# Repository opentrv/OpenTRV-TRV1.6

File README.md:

# OpenTRV-TRV1.6
TRV1.6 smart thermostatic radiator valve hardware and software,
evolved from TRV1.5/REV7.

A 'V0p2' type (ATmega328P) board with an alternative motor driver.

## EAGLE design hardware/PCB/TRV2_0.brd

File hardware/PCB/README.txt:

Location for TRV2 schematic and PCB.

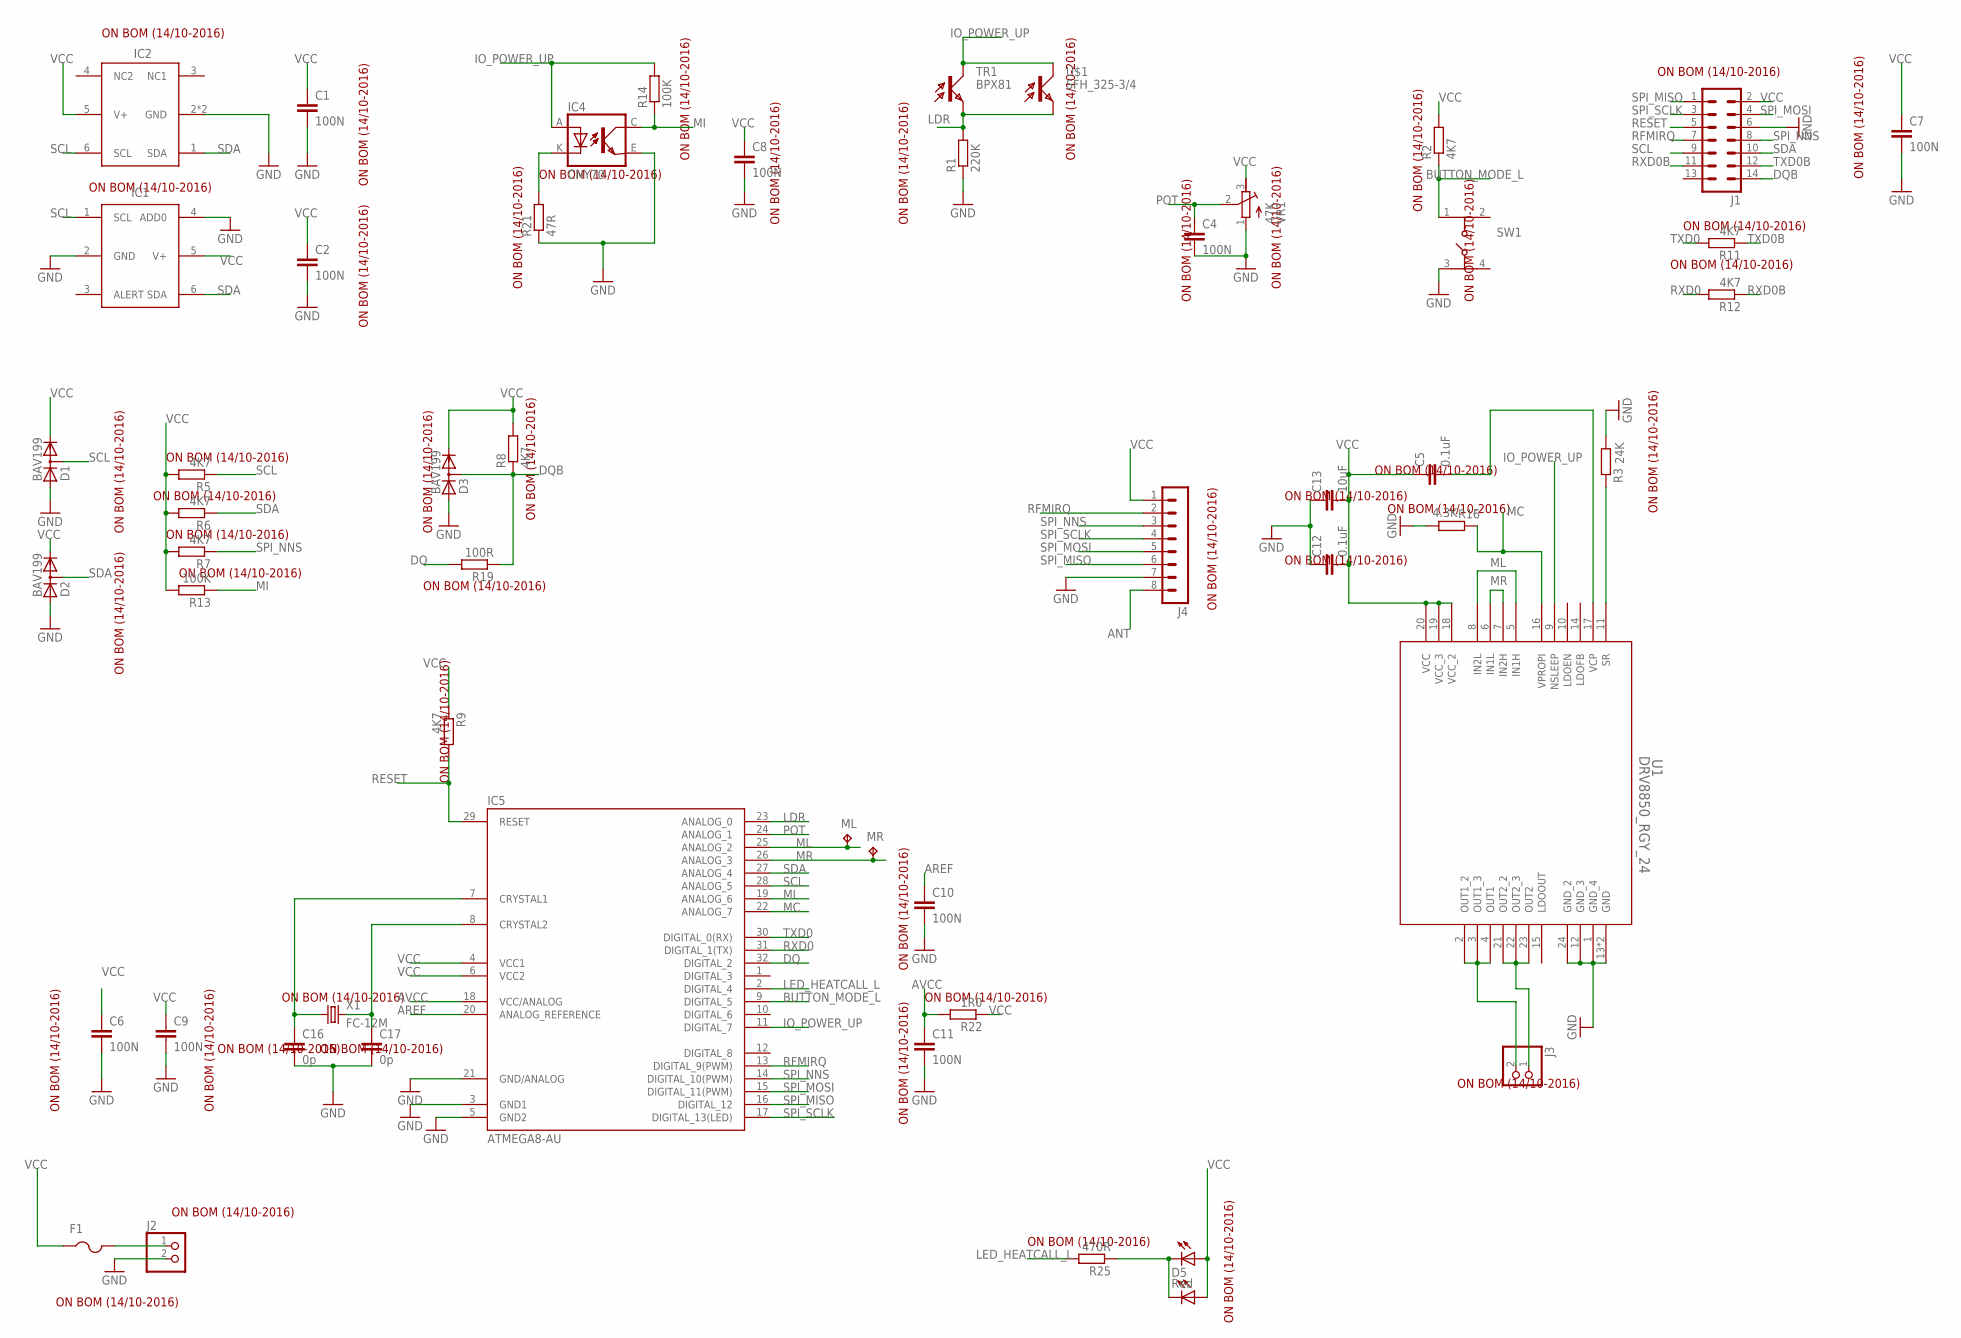
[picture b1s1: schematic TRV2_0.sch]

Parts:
C1, C2, C4, C6, C7, C8, C9, C10, C11: 100N; C0603
C5, C12: 0.1uF; C0603
C13: 10uF; C0603
C16, C17: 0p; C0603
D1, D2, D3: BAV199; SOT23
D5: Red; LED3MM
F1: PTCFUSE-0603; CHIPLED-0603-TTW
IC1: TMP112
IC2: IC2; SHT21
IC4: CNY70; 4
IC5: ATMEGA8-AU; TQFP32-08
J1: MA07-2
J2, J3: PINHD-1X2; 1X02
J4: MA08-1
ML: TPB1,27; B1,27
MR: TPB1,27; B1,27
R1: 220K; R0603
R2, R5, R6, R7, R8, R9, R11, R12: 4K7; R0603
R3: 24K; R0603
R13, R14: 100K; R0603
R16: 4.3K; R0603
R19: 100R; R0603
R21: 47R; R0603
R22: 1R0; R0603
R25: 470R; R0603
SW1: 434331013822
TR1: BPX81
U1: DRV8850_RGY_24; RGY_24
U$1: SFH_325-3/4
U$2: KINGBRIGHTSIDELED
VR1: 47K; RTRIM3296W
X1: FC-12M

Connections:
ANT: J4.8
AREF: C10.1, IC5.20 (ANALOG_REFERENCE)
AVCC: C11.1, IC5.18 (VCC/ANALOG), R22.2
BUTTON_MODE_L: IC5.9 (DIGITAL_5), R2.1, SW1.1
DQ: IC5.32 (DIGITAL_2), R19.2
DQB: D3.3 (AC), J1.14, R8.1, R19.1
GND: C1.2, C2.2, C4.2, C6.2, C7.2, C8.2, C9.2, C10.2, C11.2, C12.1, C13.1, C16.2, C17.2, D1.1 (A), D2.1 (A), D3.1 (A), IC1.2 (GND), IC1.4 (ADD0), IC2.2 (GND), IC2.P$1 (GND), IC4.E (EMI), IC5.3 (GND1), IC5.5 (GND2), IC5.21 (GND/ANALOG), J1.6, J2.2, J4.7, R1.1, R3.1, R16.1, R21.1, SW1.3, U1.1 (GND_4), U1.12 (GND_3), U1.13 (GND), U1.24 (GND_2), U1.25 (GND), VR1.1 (A)
IO_POWER_UP: IC4.A, IC5.11 (DIGITAL_7), R14.2, TR1.C, U1.9 (NSLEEP), U$1.P$2 (C)
LDR: IC5.23 (ANALOG_0), R1.2, TR1.E, U$1.P$1 (E)
LED_HEATCALL_L: IC5.2 (DIGITAL_4), R25.2
MC: IC5.22 (ANALOG_7), R16.2, U1.16 (VPROPI)
MI: IC4.C (COL), IC5.19 (ANALOG_6), R13.1, R14.1
ML: IC5.25 (ANALOG_2), ML.TP, U1.5 (IN1H), U1.8 (IN2L)
MR: IC5.26 (ANALOG_3), MR.TP, U1.6 (IN1L), U1.7 (IN2H)
unnamed: IC4.K (C), R21.2
unnamed: J3.2, U1.2 (OUT1_2), U1.3 (OUT1_3), U1.4 (OUT1)
unnamed: C16.1, IC5.7 (CRYSTAL1), X1.1
unnamed: C17.1, IC5.8 (CRYSTAL2), X1.2
unnamed: D5.K (C), R25.1, U$2.C
unnamed: F1.C (2), J2.1
unnamed: J3.1, U1.21 (OUT2_2), U1.22 (OUT2_3), U1.23 (OUT2)
unnamed: R3.2, U1.11 (SR)
unnamed: C5.2, U1.17 (VCP)
POT: C4.1, IC5.24 (ANALOG_1), VR1.2 (S)
RESET: IC5.29 (RESET), J1.5, R9.2
RFMIRQ: IC5.13 (DIGITAL_9(PWM)), J1.7, J4.2
RXD0: IC5.31 (DIGITAL_1(TX)), R12.2
RXD0B: J1.11, R12.1
SCL: D1.3 (AC), IC1.1 (SCL), IC2.6 (SCL), IC5.28 (ANALOG_5), J1.9, R5.1
SDA: D2.3 (AC), IC1.6 (SDA), IC2.1 (SDA), IC5.27 (ANALOG_4), J1.10, R6.1
SPI_MISO: IC5.16 (DIGITAL_12), J1.1, J4.6
SPI_MOSI: IC5.15 (DIGITAL_11(PWM)), J1.4, J4.5
SPI_NNS: IC5.14 (DIGITAL_10(PWM)), J1.8, J4.3, R7.1
SPI_SCLK: IC5.17 (DIGITAL_13(LED)), J1.3, J4.4
TXD0: IC5.30 (DIGITAL_0(RX)), R11.2
TXD0B: J1.12, R11.1
VCC: C1.1, C2.1, C5.1, C6.1, C7.1, C8.1, C9.1, C12.2, C13.2, D1.2 (C), D2.2 (C), D3.2 (C), D5.A, F1.A (1), IC1.5 (V+), IC2.5 (V+), IC5.4 (VCC1), IC5.6 (VCC2), J1.2, J4.1, R2.2, R5.2, R6.2, R7.2, R8.2, R9.1, R13.2, R22.1, U1.18 (VCC_2), U1.19 (VCC_3), U1.20 (VCC), U$2.A, VR1.3 (E)

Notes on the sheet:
IC2
IC1
ON BOM (14/10-2016)

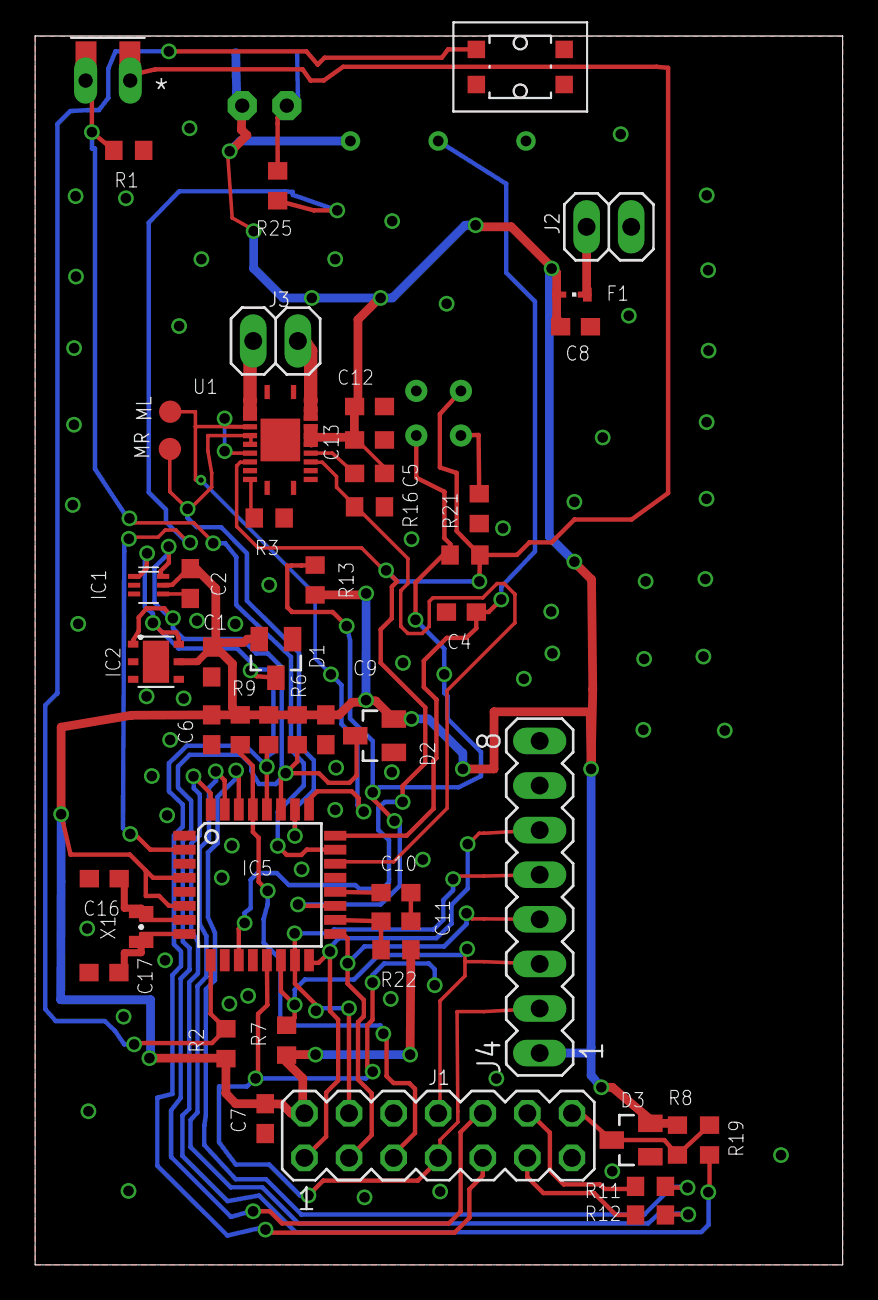
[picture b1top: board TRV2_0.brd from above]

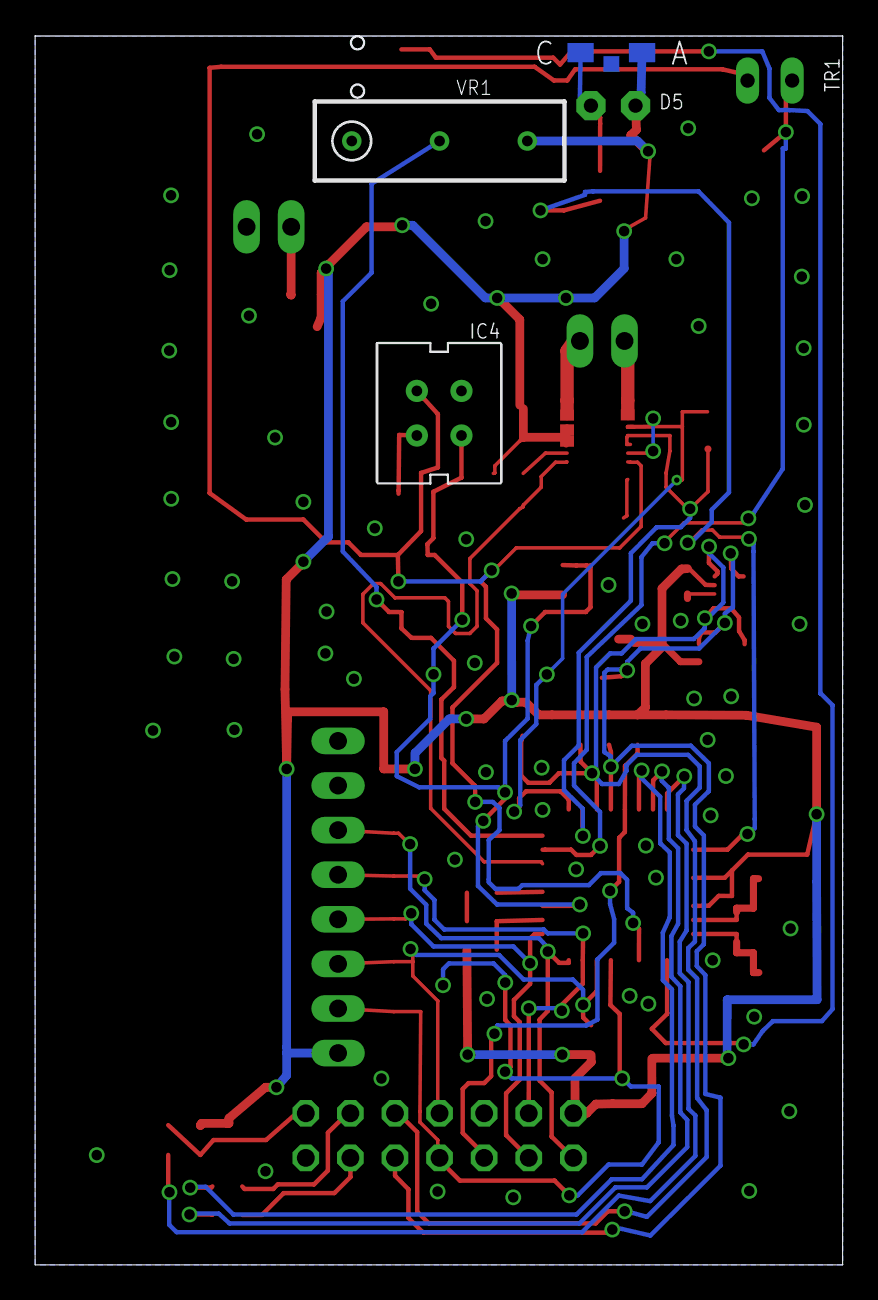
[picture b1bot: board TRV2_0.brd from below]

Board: 2 copper layers, 46.0 x 70.0 mm, 53 parts (5 on the bottom side), 36 nets.

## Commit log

2016-10-02 Convert to Eclipse general project.
2016-10-03 Create place for PCB.
2016-10-04 Schematic done
    NOTE: INT on light sensor not found anywhere else on schematic.
    NOTE: Comms connector differs from Standard.
2016-10-04 double checked schematic
2016-10-04 Typo + more explanation.
2016-10-04 first draft of board added
2016-10-04 Componets rotated and locked
    locked as they now point the same way as the one made by enlight
2016-10-04 PNG's and PDF added
2016-10-05 Thumbs.db should not be checked in.
2016-10-05 added motor header
2016-10-05 png's generated
2016-10-06 cleaned up
    Issues this far
    >>>- We don't want the RFM23B on this model (Damon, do we want to keep
    the footprint?)
    >>>- We want TR1 and D5 to be SMD devices with the 'active' side on the
    top edge of the board.
    >>>-Why does comms connector not use our standard 100%? pin8 was not
2016-10-07 removed RFM
    8 pin header is just placeholder for now
2016-10-10 SMD LED and photo added
2016-10-11 png's updated and motordriver placed on board
2016-10-12 changes as pr deniz requests
2016-10-12 Motor driver conncedted
2016-10-12 enlight board tracks added on layer 229 & 230
2016-10-12 intial "core" tracks layed out
    copy of tracks as per enlight
2016-10-13 Before routing tracks
2016-10-13 3 wires left
2016-10-13 2 wires left
2016-10-13 all wires done - need to do ERC and DRC
2016-10-13 ERC done - need to add fuse value
2016-10-14 DRV8850 lbr added and a whole BIG lot of DRC's sorted
2016-10-14 near done :-D
2016-10-14 before gerbers
2016-10-14 ready for gerbers
2016-10-14 Added DRU to project,
2016-10-14 generated gerbers + zip
2016-10-14 added power to radio module connector
2016-10-14 deleted old one
2016-10-14 More GND Via's added
2016-10-14 did not save all
2016-10-17 Added draft BOM as .ods
2016-10-20 better xtal clearance and pot on io_powerup
2016-12-21 Added minimal test sketch
2017-01-03 Fixed minimal test
2017-01-03 Added constantly updating test for sensors
2017-01-03 Updated copyrights
2017-01-03 Added hex files
2017-01-04 Updated docs
2017-01-16 working on motor driver
2017-03-17 Fixed compilation
2017-03-17 compilation actually fixed
2017-04-01 IRC notifications
2017-04-21 TRV2.5 design in KiCAD
2018-01-18 Rename trv2_compilation_test.sh to trv_compilation_test.sh

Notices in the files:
parts and their libraries:
EAGLE-TACT_SWITCHES-rev16e: Copyright: Würth Elektronik
SparkFun-Aesthetics: Licensing: CC v3.0 Share-Alike You are welcome to use this library for commercial purposes.
